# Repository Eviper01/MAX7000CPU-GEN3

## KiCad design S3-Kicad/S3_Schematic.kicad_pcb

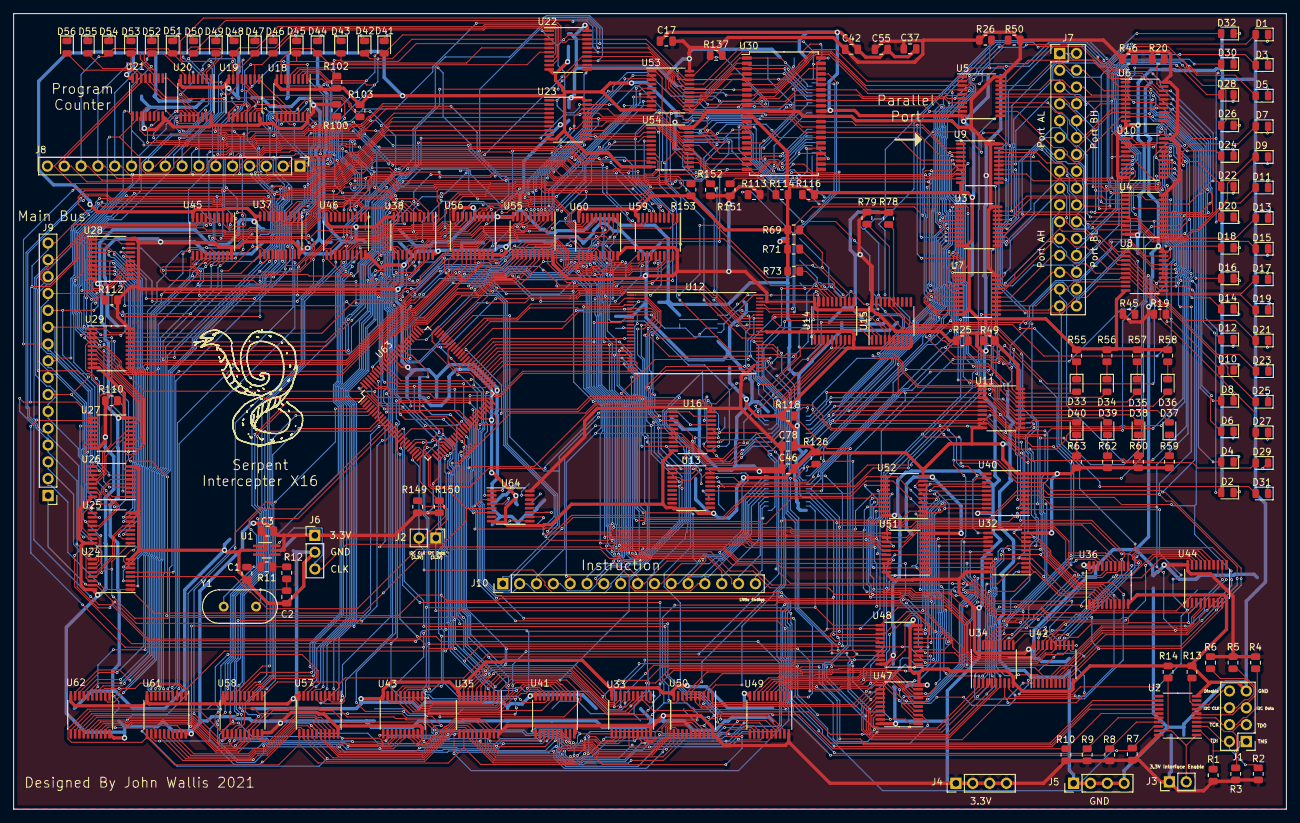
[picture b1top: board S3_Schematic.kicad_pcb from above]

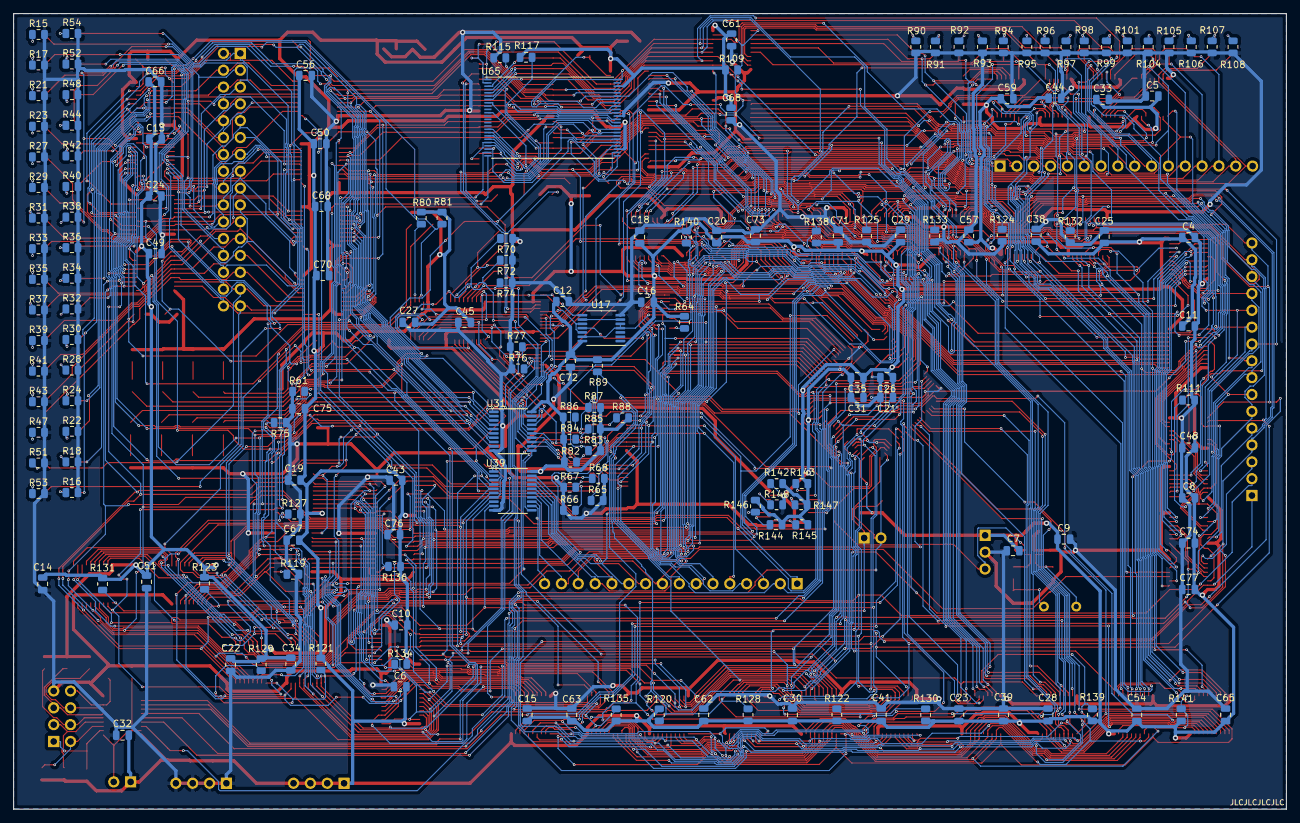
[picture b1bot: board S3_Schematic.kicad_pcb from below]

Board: 2 copper layers, 192.0 x 120.0 mm, 355 parts (167 on the bottom side), 363 nets.

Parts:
C1, C2: 32p; C_0805_2012Metric
C3, C4, C5, C6, C7, C8, C9, C10, C11, C12, C13, C14, C15, C16, C17, C18, C19, C20, C21, C22, C23, C24, C25, C26, C27, C28, C29, C30, C31, C32, C33, C34, C35, C37, C38, C39, C41, C42, C43, C44, C45, C46, C48, C49, C50, C51, C54, C55, C56, C57, C59, C60, C61, C62, C63, C65, C66, C67, C68, C71, C72, C73, C74, C75, C76, C77, C78: 100n; C_0805_2012Metric
C70: 100; C_0805_2012Metric
D1, D2, D3, D4, D5, D6, D7, D8, D9, D10, D11, D12, D13, D14, D15, D16, D17, D18, D19, D20, D21, D22, D23, D24, D25, D26, D27, D28, D29, D30, D31, D32, D33, D34, D35, D36, D37, D38, D39, D40, D41, D42, D43, D44, D45, D46, D47, D48, D49, D50, D51, D52, D53, D54, D55, D56: LED; LED_0805_2012Metric
J1: Conn_02x04_Counter_Clockwise; PinHeader_2x04_P2.54mm_Vertical
J2, J3: Conn_01x02; PinHeader_1x02_P2.54mm_Vertical
J4, J5: Conn_01x04; PinHeader_1x04_P2.54mm_Vertical
J6: Conn_01x03; PinHeader_1x03_P2.54mm_Vertical
J7: Conn_02x16_Odd_Even; PinHeader_2x16_P2.54mm_Vertical
J8, J9, J10: Conn_01x16; PinHeader_1x16_P2.54mm_Vertical
R1, R2, R3, R4, R5, R6, R7, R8, R9, R10, R13, R14, R19, R20, R25, R26, R45, R46, R49, R50, R61, R64, R65, R66, R67, R68, R69, R70, R71, R72, R73, R74, R75, R76, R77, R78, R79, R80, R81, R82, R83, R84, R85, R86, R87, R88, R89, R100, R102, R103, R109, R110, R111, R112, R113, R114, R115, R116, R117, R118, R119, R120, R121, R122, R123, R124, R125, R126, R127, R128, R129, R130, R131, R132, R133, R134, R135, R136, R137, R138, R139, R140, R141, R142, R143, R144, R145, R146, R147, R148, R149, R150, R151, R152, R153: 50K; R_0805_2012Metric
R11: 2.2M; R_0805_2012Metric
R12: 1k; R_0805_2012Metric
R15, R16, R17, R18, R21, R22, R23, R24, R27, R28, R29, R30, R31, R32, R33, R34, R35, R36, R37, R38, R39, R40, R41, R42, R43, R44, R47, R48, R51, R52, R53, R54, R55, R56, R57, R58, R59, R60, R62, R63, R90, R91, R92, R93, R94, R95, R96, R97, R98, R99, R101, R104, R105, R106, R107, R108: 330; R_0805_2012Metric
U1: SN74LVC1GX04DCKR; SOT-363_SC-70-6_Handsoldering
U2, U4, U6, U8, U10, U13, U14, U15, U16, U22, U23, U28, U29, U47, U48, U49, U50, U51, U52, U53, U54, U55, U56, U57, U58, U59, U60, U61, U62: 74HC541; TSSOP-20_4.4x6.5mm_P0.65mm
U3, U5, U7, U9, U11, U31, U32, U33, U34, U35, U36, U37, U38, U39, U40, U41, U42, U43, U44, U45, U46: 74HC574; TSSOP-20_4.4x6.5mm_P0.65mm
U12, U65: SST39VF800A-70-4C-EKE; TSOP-I-48_18.4x12mm_P0.5mm
U17: 74HC00; TSSOP-14_4.4x5mm_P0.65mm
U18, U19, U20, U21, U24, U25, U26, U27, U64: 74hc193; TSSOP-16_4.4x5mm_P0.65mm
U30: CY62136EV30LL-45ZSXI; TSOP-II-44_10.16x18.41mm_P0.8mm
U63: XC9572XL-10TQG100C; TQFP-100_14x14mm_P0.5mm
Y1: Crystal; Crystal_HC49-U_Vertical

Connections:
+3V3: C3.1, C4.1, C5.1, C6.1, C7.1, C8.1, C9.1, C10.1, C11.1, C12.1, C13.1, C14.1, C15.1, C16.1, C17.1, C18.1, C19.1, C20.1, C21.1, C22.1, C23.1, C24.1, C25.1, C26.1, C27.1, C28.1, C29.1, C30.1, C31.1, C32.1, C33.1, C34.1, C35.1, C37.1, C38.1, C39.1, C41.1, C42.1, C43.1, C44.1, C45.1, C46.1, C48.1, C49.1, C50.1, C51.1, C54.1, C55.1, C56.1, C57.1, C59.1, C60.1, C61.1, C62.1, C63.1, C65.1, C66.1, C67.1, C68.1, C70.1, C71.1, C72.1, C73.1, C74.1, C75.1, C76.1, C77.1, C78.1, J3.1, J4.1, J4.2, J4.3, J4.4, J6.1, R1.1, R2.1, R3.1, R4.1, R5.1, R6.1, R7.1, R8.1, R9.1, R10.1, R19.1, R20.1, R25.1, R26.1, R45.1, R46.1, R49.1, R50.1, R64.1, R78.1, R79.1, R80.1, R81.1, R82.1, R83.1, R84.1, R85.1, R86.1, R87.1, R88.1, R89.1, R100.1, R109.2, R110.1, R112.2, R113.2, R117.2, R120.2, R121.2, R122.2, R123.2, R128.2, R129.2, R130.2, R131.2, R134.1, R135.1, R136.1, R137.1, R138.1, R139.1, R140.1, R141.1, R142.1, R143.1, R144.1, R145.1, R146.1, R147.1, R149.1, R150.1, R151.1, R152.1, U1.5, U2.20, U3.20, U4.20, U5.20, U6.20, U7.20, U8.20, U9.20, U10.20, U11.20, U12.27, U12.46, U13.20, U14.20, U15.20, U16.20, U17.14, U18.16, U19.16, U20.16, U21.16, U22.20, U23.20, U24.16, U25.16, U26.16, U27.16, U28.20, U29.20, U30.11, U30.33, U31.20, U32.20, U33.20, U34.20, U35.20, U36.20, U37.20, U38.20, U39.20, U40.20, U41.20, U42.20, U43.20, U44.20, U45.20, U46.20, U47.20, U48.20, U49.20, U50.20, U51.20, U52.20, U53.20, U54.20, U55.20, U56.20, U57.20, U58.20, U59.20, U60.20, U61.20, U62.20, U63.26, U63.38, U63.51, U63.88, U64.16, U65.27, U65.46
/ALU/B0: J9.1, U3.2, U4.18, U5.2, U6.18, U11.2, U24.15, U30.7, U31.2, U32.2, U33.2, U34.2, U35.2, U36.2, U37.2, U38.2, U47.18, U63.52, U65.45
/ALU/B1: J9.2, U3.3, U4.17, U5.3, U6.17, U11.3, U24.1, U30.8, U31.3, U32.3, U33.3, U34.3, U35.3, U36.3, U37.3, U38.3, U47.17, U63.50, U65.44
/ALU/B2: J9.3, U3.4, U4.16, U5.4, U6.16, U11.4, U24.10, U30.9, U31.4, U32.4, U33.4, U34.4, U35.4, U36.4, U37.4, U38.4, U47.16, U63.49, U65.43
/ALU/B3: J9.4, U3.5, U4.15, U5.5, U6.15, U11.5, U24.9, U30.10, U31.5, U32.5, U33.5, U34.5, U35.5, U36.5, U37.5, U38.5, U47.15, U63.42, U65.42
/ALU/B4: J9.5, U3.6, U4.14, U5.6, U6.14, U11.6, U25.15, U30.38, U31.6, U32.6, U33.6, U34.6, U35.6, U36.6, U37.6, U38.6, U47.14, U63.41, U65.41
/ALU/B5: J9.6, U3.7, U4.13, U5.7, U6.13, U11.7, U25.1, U30.37, U31.7, U32.7, U33.7, U34.7, U35.7, U36.7, U37.7, U38.7, U47.13, U63.40, U65.40
/ALU/B6: J9.7, U3.8, U4.12, U5.8, U6.12, U11.8, U25.10, U30.36, U31.8, U32.8, U33.8, U34.8, U35.8, U36.8, U37.8, U38.8, U47.12, U63.39, U65.39
/ALU/B7: J9.8, U3.9, U4.11, U5.9, U6.11, U11.9, U25.9, U30.35, U31.9, U32.9, U33.9, U34.9, U35.9, U36.9, U37.9, U38.9, U47.11, U63.37, U65.38
/ALU/B8: J9.9, U7.2, U8.18, U9.2, U10.18, U26.15, U30.32, U39.2, U40.2, U41.2, U42.2, U43.2, U44.2, U45.2, U46.2, U48.18, U63.36, U65.36
/ALU/B9: J9.10, U7.3, U8.17, U9.3, U10.17, U26.1, U30.31, U39.3, U40.3, U41.3, U42.3, U43.3, U44.3, U45.3, U46.3, U48.17, U63.35, U65.35
/ALU/B10: J9.11, U7.4, U8.16, U9.4, U10.16, U26.10, U30.30, U39.4, U40.4, U41.4, U42.4, U43.4, U44.4, U45.4, U46.4, U48.16, U63.33, U65.34
/ALU/B11: J9.12, U7.5, U8.15, U9.5, U10.15, U26.9, U30.29, U39.5, U40.5, U41.5, U42.5, U43.5, U44.5, U45.5, U46.5, U48.15, U63.32, U65.33
/ALU/B12: J9.13, U7.6, U8.14, U9.6, U10.14, U27.15, U30.16, U39.6, U40.6, U41.6, U42.6, U43.6, U44.6, U45.6, U46.6, U48.14, U63.30, U65.32
/ALU/B13: J9.14, U7.7, U8.13, U9.7, U10.13, U27.1, U30.15, U39.7, U40.7, U41.7, U42.7, U43.7, U44.7, U45.7, U46.7, U48.13, U63.29, U65.31
/ALU/B14: J9.15, U7.8, U8.12, U9.8, U10.12, U27.10, U30.14, U39.8, U40.8, U41.8, U42.8, U43.8, U44.8, U45.8, U46.8, U48.12, U63.28, U65.30
/ALU/B15: J9.16, U7.9, U8.11, U9.9, U10.11, U27.9, U30.13, U39.9, U40.9, U41.9, U42.9, U43.9, U44.9, U45.9, U46.9, U48.11, U63.27, U65.29
/ALU/EvenR0: U34.19, U36.19, U51.18, U55.18, U59.18, U63.71
/ALU/EvenR1: U34.18, U36.18, U51.17, U55.17, U59.17, U63.72
/ALU/EvenR2: U34.17, U36.17, U51.16, U55.16, U59.16, U63.74
/ALU/EvenR3: U34.16, U36.16, U51.15, U55.15, U59.15, U63.76
/ALU/EvenR4: U34.15, U36.15, U51.14, U55.14, U59.14, U63.77
/ALU/EvenR5: U34.14, U36.14, U51.13, U55.13, U59.13, U63.78
/ALU/EvenR6: U34.13, U36.13, U51.12, U55.12, U59.12, U63.79
/ALU/EvenR7: U34.12, U36.12, U51.11, U55.11, U59.11, U63.81
/ALU/EvenR8: U42.19, U44.19, U52.18, U56.18, U60.18, U63.82
/ALU/EvenR9: U42.18, U44.18, U52.17, U56.17, U60.17, U63.85
/ALU/EvenR10: U42.17, U44.17, U52.16, U56.16, U60.16, U63.86
/ALU/EvenR11: U42.16, U44.16, U52.15, U56.15, U60.15, U63.87
/ALU/EvenR12: U42.15, U44.15, U52.14, U56.14, U60.14, U63.89
/ALU/EvenR13: U42.14, U44.14, U52.13, U56.13, U60.13, U63.90
/ALU/EvenR14: U42.13, U44.13, U52.12, U56.12, U60.12, U63.91
/ALU/EvenR15: U42.12, U44.12, U52.11, U56.11, U60.11, U63.92
/ALU/Ins0: J10.1, U12.48, U13.2, U14.2, U15.2, U16.2, U31.19, U63.70
/ALU/Ins1: J10.2, U12.1, U13.3, U14.3, U15.3, U16.3, U31.18, U63.68
/ALU/Ins2: J10.3, U12.2, U13.4, U14.4, U15.4, U16.4, U31.17, U63.67
/ALU/Ins3: J10.4, U12.3, U13.5, U14.5, U15.5, U16.5, U31.16, U63.66
/ALU/Ins4: J10.5, U12.4, U14.6, U16.6, U31.15, U63.65
/ALU/Ins5: J10.6, U12.5, U14.7, U16.7, U31.14, U63.64
/ALU/Ins6: J10.7, U12.6, U14.8, U16.8, U31.13, U63.63
/ALU/Ins7: J10.8, U12.7, U16.9, U17.4, U17.5, U17.13, U31.12, U63.61
/ALU/Ins8: J10.9, U12.8, U39.19, U63.60
/ALU/Ins9: J10.10, U12.16, U39.18, U63.59
/ALU/Ins10: J10.11, U12.17, U39.17, U63.58
/ALU/Ins11: J10.12, U12.18, U39.16, U63.57
/ALU/Ins12: J10.13, U12.19, U39.15, U63.56
/ALU/Ins13: J10.14, U12.20, U39.14, U63.55
/ALU/Ins14: J10.15, U12.21, U39.13, U63.54
/ALU/Ins15: J10.16, U12.22, U39.12, U63.53
/ALU/OddR0: U33.19, U35.19, U49.18, U57.18, U61.18, U63.18
/ALU/OddR1: U33.18, U35.18, U49.17, U57.17, U61.17, U63.17
/ALU/OddR2: U33.17, U35.17, U49.16, U57.16, U61.16, U63.16
/ALU/OddR3: U33.16, U35.16, U49.15, U57.15, U61.15, U63.15
/ALU/OddR4: U33.15, U35.15, U49.14, U57.14, U61.14, U63.14
/ALU/OddR5: U33.14, U35.14, U49.13, U57.13, U61.13, U63.13
/ALU/OddR6: U33.13, U35.13, U49.12, U57.12, U61.12, U63.12
/ALU/OddR7: U33.12, U35.12, U49.11, U57.11, U61.11, U63.11
/ALU/OddR8: U41.19, U43.19, U50.18, U58.18, U62.18, U63.10
/ALU/OddR9: U41.18, U43.18, U50.17, U58.17, U62.17, U63.9
/ALU/OddR10: U41.17, U43.17, U50.16, U58.16, U62.16, U63.8
/ALU/OddR11: U41.16, U43.16, U50.15, U58.15, U62.15, U63.6
/ALU/OddR12: U41.15, U43.15, U50.14, U58.14, U62.14, U63.5
/ALU/OddR13: U41.14, U43.14, U50.13, U58.13, U62.13, U63.4
/ALU/OddR14: U41.13, U43.13, U50.12, U58.12, U62.12, U63.3
/ALU/OddR15: U41.12, U43.12, U50.11, U58.11, U62.11, U63.1
/ALU/State0: U12.23, U63.99, U64.3
/ALU/State1: U12.24, U63.98, U64.2
/ALU/State2: U12.25, U63.97, U64.6
/Boot Flash/MA0: U22.18, U28.18, U30.42, U53.18, U65.48
/Boot Flash/MA1: U22.17, U28.17, U30.43, U53.17, U65.1
/Boot Flash/MA2: U22.16, U28.16, U30.44, U53.16, U65.2
/Boot Flash/MA3: U22.15, U28.15, U30.1, U53.15, U65.3
/Boot Flash/MA4: U22.14, U28.14, U30.2, U53.14, U65.4
/Boot Flash/MA5: U22.13, U28.13, U30.3, U53.13, U65.5
/Boot Flash/MA6: U22.12, U28.12, U30.4, U53.12, U65.6
/Boot Flash/MA7: U22.11, U28.11, U30.5, U53.11, U65.7
/Boot Flash/MA8: U23.18, U29.18, U30.18, U54.18, U65.8
/Boot Flash/MA9: U23.17, U29.17, U30.19, U54.17, U65.16
/Boot Flash/MA10: U23.16, U29.16, U30.20, U54.16, U65.17
/Boot Flash/MA11: U23.15, U29.15, U30.21, U54.15, U65.18
/Boot Flash/MA12: U23.14, U29.14, U30.22, U54.14, U65.19
/Boot Flash/MA13: U23.13, U29.13, U30.25, U54.13, U65.20
/Boot Flash/MA14: U23.12, U29.12, U30.26, U54.12, U65.21
/Boot Flash/MA15: U23.11, U29.11, U30.27, U54.11, U65.22
/GPIO/P0: D1.2, J7.1, U3.19, U4.2
/GPIO/P1: D3.2, J7.3, U3.18, U4.3
/GPIO/P2: D5.2, J7.5, U3.17, U4.4
/GPIO/P3: D7.2, J7.7, U3.16, U4.5
/GPIO/P4: D9.2, J7.9, U3.15, U4.6
/GPIO/P5: D11.2, J7.11, U3.14, U4.7
/GPIO/P6: D13.2, J7.13, U3.13, U4.8
/GPIO/P7: D15.2, J7.15, U3.12, U4.9
/GPIO/P8: D17.2, J7.17, U7.19, U8.2
/GPIO/P9: D19.2, J7.19, U7.18, U8.3
/GPIO/P10: D21.2, J7.21, U7.17, U8.4
/GPIO/P11: D23.2, J7.23, U7.16, U8.5
/GPIO/P12: D25.2, J7.25, U7.15, U8.6
/GPIO/P13: D27.2, J7.27, U7.14, U8.7
/GPIO/P14: D29.2, J7.29, U7.13, U8.8
/GPIO/P15: D31.2, J7.31, U7.12, U8.9
/GPIO/P16: D32.2, J7.32, U9.12, U10.9
/GPIO/P17: D30.2, J7.30, U9.13, U10.8
/GPIO/P18: D28.2, J7.28, U9.14, U10.7
/GPIO/P19: D26.2, J7.26, U9.15, U10.6
/GPIO/P20: D24.2, J7.24, U9.16, U10.5
/GPIO/P21: D22.2, J7.22, U9.17, U10.4
/GPIO/P22: D20.2, J7.20, U9.18, U10.3
/GPIO/P23: D18.2, J7.18, U9.19, U10.2
/GPIO/P24: D16.2, J7.16, U5.12, U6.9
/GPIO/P25: D14.2, J7.14, U5.13, U6.8
/GPIO/P26: D12.2, J7.12, U5.14, U6.7
/GPIO/P27: D10.2, J7.10, U5.15, U6.6
/GPIO/P28: D8.2, J7.8, U5.16, U6.5
/GPIO/P29: D6.2, J7.6, U5.17, U6.4
/GPIO/P30: D4.2, J7.4, U5.18, U6.3
/GPIO/P31: D2.2, J7.2, U5.19, U6.2
/ProgramCounter/JB0: U18.15, U37.19, U59.2, U61.2
/ProgramCounter/JB1: U18.1, U37.18, U59.3, U61.3
/ProgramCounter/JB2: U18.10, U37.17, U59.4, U61.4
/ProgramCounter/JB3: U18.9, U37.16, U59.5, U61.5
/ProgramCounter/JB4: U19.15, U37.15, U59.6, U61.6
/ProgramCounter/JB5: U19.1, U37.14, U59.7, U61.7
/ProgramCounter/JB6: U19.10, U37.13, U59.8, U61.8
/ProgramCounter/JB7: U19.9, U37.12, U59.9, U61.9
/ProgramCounter/JB8: U20.15, U45.19, U60.2, U62.2
/ProgramCounter/JB9: U20.1, U45.18, U60.3, U62.3
/ProgramCounter/JB10: U20.10, U45.17, U60.4, U62.4
/ProgramCounter/JB11: U20.9, U45.16, U60.5, U62.5
/ProgramCounter/JB12: U21.15, U45.15, U60.6, U62.6
/ProgramCounter/JB13: U21.1, U45.14, U60.7, U62.7
/ProgramCounter/JB14: U21.10, U45.13, U60.8, U62.8
/ProgramCounter/JB15: U21.9, U45.12, U60.9, U62.9
/ProgramCounter/PC0: D41.2, J8.1, U18.3, U22.2
/ProgramCounter/PC1: D42.2, J8.2, U18.2, U22.3
/ProgramCounter/PC2: D43.2, J8.3, U18.6, U22.4
/ProgramCounter/PC3: D44.2, J8.4, U18.7, U22.5
/ProgramCounter/PC4: D45.2, J8.5, U19.3, U22.6
/ProgramCounter/PC5: D46.2, J8.6, U19.2, U22.7
/ProgramCounter/PC6: D47.2, J8.7, U19.6, U22.8
/ProgramCounter/PC7: D48.2, J8.8, U19.7, U22.9
/ProgramCounter/PC8: D49.2, J8.9, U20.3, U23.2
/ProgramCounter/PC9: D50.2, J8.10, U20.2, U23.3
/ProgramCounter/PC10: D51.2, J8.11, U20.6, U23.4
/ProgramCounter/PC11: D52.2, J8.12, U20.7, U23.5
/ProgramCounter/PC12: D53.2, J8.13, U21.3, U23.6
/ProgramCounter/PC13: D54.2, J8.14, U21.2, U23.7
/ProgramCounter/PC14: D55.2, J8.15, U21.6, U23.8
/ProgramCounter/PC15: D56.2, J8.16, U21.7, U23.9
/Registers/Acc0: U32.19, U47.2, U49.2, U51.2
/Registers/Acc1: U32.18, U47.3, U49.3, U51.3
/Registers/Acc2: U32.17, U47.4, U49.4, U51.4
/Registers/Acc3: U32.16, U47.5, U49.5, U51.5
/Registers/Acc4: U32.15, U47.6, U49.6, U51.6
/Registers/Acc5: U32.14, U47.7, U49.7, U51.7
/Registers/Acc6: U32.13, U47.8, U49.8, U51.8
/Registers/Acc7: U32.12, U47.9, U49.9, U51.9
/Registers/Acc8: U40.19, U48.2, U50.2, U52.2
/Registers/Acc9: U40.18, U48.3, U50.3, U52.3
/Registers/Acc10: U40.17, U48.4, U50.4, U52.4
/Registers/Acc11: U40.16, U48.5, U50.5, U52.5
/Registers/Acc12: U40.15, U48.6, U50.6, U52.6
/Registers/Acc13: U40.14, U48.7, U50.7, U52.7
/Registers/Acc14: U40.13, U48.8, U50.8, U52.8
/Registers/Acc15: U40.12, U48.9, U50.9, U52.9
/Registers/RA0: U38.19, U53.2, U55.2, U57.2
/Registers/RA1: U38.18, U53.3, U55.3, U57.3
/Registers/RA2: U38.17, U53.4, U55.4, U57.4
/Registers/RA3: U38.16, U53.5, U55.5, U57.5
/Registers/RA4: U38.15, U53.6, U55.6, U57.6
/Registers/RA5: U38.14, U53.7, U55.7, U57.7
/Registers/RA6: U38.13, U53.8, U55.8, U57.8
/Registers/RA7: U38.12, U53.9, U55.9, U57.9
/Registers/RA8: U46.19, U54.2, U56.2, U58.2
/Registers/RA9: U46.18, U54.3, U56.3, U58.3
/Registers/RA10: U46.17, U54.4, U56.4, U58.4
/Registers/RA11: U46.16, U54.5, U56.5, U58.5
/Registers/RA12: U46.15, U54.6, U56.6, U58.6
/Registers/RA13: U46.14, U54.7, U56.7, U58.7
/Registers/RA14: U46.13, U54.8, U56.8, U58.8
/Registers/RA15: U46.12, U54.9, U56.9, U58.9
/StackPointer/SP0: U24.3, U28.2
/StackPointer/SP1: U24.2, U28.3
/StackPointer/SP2: U24.6, U28.4
/StackPointer/SP3: U24.7, U28.5
/StackPointer/SP4: U25.3, U28.6
/StackPointer/SP5: U25.2, U28.7
/StackPointer/SP6: U25.6, U28.8
/StackPointer/SP7: U25.7, U28.9
/StackPointer/SP8: U26.3, U29.2
/StackPointer/SP9: U26.2, U29.3
/StackPointer/SP10: U26.6, U29.4
/StackPointer/SP11: U26.7, U29.5
/StackPointer/SP12: U27.3, U29.6
/StackPointer/SP13: U27.2, U29.7
/StackPointer/SP14: U27.6, U29.8
/StackPointer/SP15: U27.7, U29.9
CLK: J6.3, U1.6, U63.22, U64.5
CounterClear: R103.2, U18.14, U19.14, U20.14, U21.14
CounterUp: U12.42, U18.5
DDR_Load: R75.2, U11.11, U14.18
FLASHPAGE0: D39.2, U11.13, U65.23
FLASHPAGE1: D38.2, U11.14, U65.24
FLASHPAGE2: D37.2, U11.15, U65.25
FlashOut: R152.2, U12.36, U65.28
GND: C1.2, C2.2, C3.2, C4.2, C5.2, C6.2, C7.2, C8.2, C9.2, C10.2, C11.2, C12.2, C13.2, C14.2, C15.2, C16.2, C17.2, C18.2, C19.2, C20.2, C21.2, C22.2, C23.2, C24.2, C25.2, C26.2, C27.2, C28.2, C29.2, C30.2, C31.2, C32.2, C33.2, C34.2, C35.2, C37.2, C38.2, C39.2, C41.2, C42.2, C43.2, C44.2, C45.2, C46.2, C48.2, C49.2, C50.2, C51.2, C54.2, C55.2, C56.2, C57.2, C59.2, C60.2, C61.2, C62.2, C63.2, C65.2, C66.2, C67.2, C68.2, C70.2, C71.2, C72.2, C73.2, C74.2, C75.2, C76.2, C77.2, C78.2, J1.7, J5.1, J5.2, J5.3, J5.4, J6.2, R13.2, R14.2, R15.2, R16.2, R17.2, R18.2, R21.2, R22.2, R23.2, R24.2, R27.2, R28.2, R29.2, R30.2, R31.2, R32.2, R33.2, R34.2, R35.2, R36.2, R37.2, R38.2, R39.2, R40.2, R41.2, R42.2, R43.2, R44.2, R47.2, R48.2, R51.2, R52.2, R53.2, R54.2, R55.2, R56.2, R57.2, R58.2, R59.2, R60.2, R61.1, R62.2, R63.2, R65.1, R66.1, R67.1, R68.1, R69.1, R70.1, R71.1, R72.1, R73.1, R74.1, R75.1, R76.1, R77.1, R90.2, R91.2, R92.2, R93.2, R94.2, R95.2, R96.2, R97.2, R98.2, R99.2, R101.2, R102.1, R103.1, R104.2, R105.2, R106.2, R107.2, R108.2, R111.1, R114.2, R115.2, R116.2, R118.2, R119.2, R124.2, R125.2, R126.2, R127.2, R132.2, R133.2, R148.1, R153.1, U1.2, U2.10, U3.10, U4.10, U5.10, U6.10, U7.10, U8.10, U9.10, U10.10, U11.10, U12.37, U13.10, U14.10, U15.10, U16.10, U17.7, U18.8, U19.8, U20.8, U21.8, U22.10, U23.10, U24.8, U25.8, U26.8, U27.8, U28.10, U29.10, U30.12, U30.34, U31.10, U32.10, U33.10, U34.10, U35.10, U36.10, U37.10, U38.10, U39.10, U40.10, U41.10, U42.10, U43.10, U44.10, U45.10, U46.10, U47.10, U48.10, U49.10, U50.10, U51.10, U52.10, U53.10, U54.10, U55.10, U56.10, U57.10, U58.10, U59.10, U60.10, U61.10, U62.10, U63.21, U63.31, U63.44, U63.62, U63.69, U63.75, U63.84, U63.100, U64.8, U65.37
InsRegControl: U12.34, U31.11, U39.11
MainRegReadControl: U12.33, U32.11, U40.11
unnamed: C1.1, R11.2, U1.3, Y1.1
unnamed: C2.1, R12.2, Y1.2
unnamed: D1.1, R15.1
unnamed: D2.1, R16.1
unnamed: D3.1, R17.1
unnamed: D4.1, R18.1
unnamed: D5.1, R21.1
unnamed: D6.1, R22.1
unnamed: D7.1, R23.1
unnamed: D8.1, R24.1
unnamed: D9.1, R27.1
unnamed: D10.1, R28.1
unnamed: D11.1, R29.1
unnamed: D12.1, R30.1
unnamed: D13.1, R31.1
unnamed: D14.1, R32.1
unnamed: D15.1, R33.1
unnamed: D16.1, R34.1
unnamed: D17.1, R35.1
unnamed: D18.1, R36.1
unnamed: D19.1, R37.1
unnamed: D20.1, R38.1
unnamed: D21.1, R39.1
unnamed: D22.1, R40.1
unnamed: D23.1, R41.1
unnamed: D24.1, R42.1
unnamed: D25.1, R43.1
unnamed: D26.1, R44.1
unnamed: D27.1, R47.1
unnamed: D28.1, R48.1
unnamed: D29.1, R51.1
unnamed: D30.1, R52.1
unnamed: D31.1, R53.1
unnamed: D32.1, R54.1
unnamed: D33.1, R55.1
unnamed: D34.1, R56.1
unnamed: D35.1, R57.1
unnamed: D36.1, R58.1
unnamed: D37.1, R59.1
unnamed: D38.1, R60.1
unnamed: D39.1, R62.1
unnamed: D40.1, R63.1
unnamed: D41.1, R90.1
unnamed: D42.1, R91.1
unnamed: D43.1, R92.1
unnamed: D44.1, R93.1
unnamed: D45.1, R94.1
unnamed: D46.1, R95.1
unnamed: D47.1, R96.1
unnamed: D48.1, R97.1
unnamed: D49.1, R98.1
unnamed: D50.1, R99.1
unnamed: D51.1, R101.1
unnamed: D52.1, R104.1
unnamed: D53.1, R105.1
unnamed: D54.1, R106.1
unnamed: D55.1, R107.1
unnamed: D56.1, R108.1
unnamed: J3.2, R14.1, U2.1, U2.19
unnamed: R11.1, R12.1, U1.4
unnamed: R61.2, U11.1
unnamed: R64.2, U12.11
unnamed: R76.2, U12.28
unnamed: R77.2, U12.26
unnamed: R102.2, U18.4
unnamed: R114.1, U30.40
unnamed: R115.1, U30.6
unnamed: R116.1, U30.39
unnamed: R119.1, U32.1
unnamed: R124.1, U37.1
unnamed: R125.1, U38.1
unnamed: R126.1, U39.1
unnamed: R127.1, U40.1
unnamed: R132.1, U45.1
unnamed: R133.1, U46.1
unnamed: R142.2, U64.15
unnamed: R143.2, U64.1
unnamed: R144.2, U64.10
unnamed: R145.2, U64.9
unnamed: R146.2, U64.11
unnamed: R147.2, U64.4
unnamed: R148.2, U64.14
unnamed: R151.2, U65.11
unnamed: R153.2, U65.26
unnamed: U17.6, U17.9
unnamed: U18.12, U19.5
unnamed: U18.13, U19.4
unnamed: U19.12, U20.5
unnamed: U19.13, U20.4
unnamed: U20.12, U21.5
unnamed: U20.13, U21.4
unnamed: U24.12, U25.5
unnamed: U24.13, U25.4
unnamed: U25.12, U26.5
unnamed: U25.13, U26.4
unnamed: U26.12, U27.5
unnamed: U26.13, U27.4
PS\2_CLK_3.3V: J2.2, R149.2, U2.13, U63.23
PS\2_CLK_5V: J1.6, R6.2, U2.7
PS\2_Data_3.3V: J2.1, R150.2, U2.14, U63.25
PS\2_Data_5V: J1.5, R5.2, U2.6
PortAWriteHigh: R67.2, U7.11, U13.17
PortAWriteLow: R68.2, U3.11, U13.18
PortBWriteHigh: R65.2, U9.11, U13.15
PortBWriteLow: R66.2, U5.11, U13.16
ProgramInsDisable: R118.1, U2.12, U31.1
ProgramInstructDisable_5V: J1.8, R13.1, U2.8
R1Control: R74.2, U14.17, U33.11, U41.11
R2Control: R73.2, U14.16, U34.11, U42.11
R3Control: R72.2, U14.15, U35.11, U43.11
R4Control: R71.2, U14.14, U36.11, U44.11
RAM_PAGE: D40.2, U11.12, U30.24
RJBControl: R70.2, U14.13, U37.11, U45.11
RMAControl: R69.2, U14.12, U38.11, U46.11
RegLatch: U12.43, U17.10, U17.12
StackClear: R111.2, U24.14, U25.14, U26.14, U27.14
StackDown: U12.41, U24.4
StackUp: U12.40, U24.5
TCK: R10.2, U2.15, U63.48
TCK_5V: J1.4, R4.2, U2.5
TDI: R8.2, U2.17, U63.45
TDI_5V: J1.2, R2.2, U2.3
TDO: R9.2, U2.16, U63.83
TDO_5V: J1.3, R3.2, U2.4
TMS: R7.2, U2.18, U63.47
TMS_5V: J1.1, R1.2, U2.2
~AHDD: D34.2, R49.2, U7.1, U11.18
~ALDD: D33.2, R25.2, U3.1, U11.19
~ALU_Enable: U16.1, U16.19, U63.20
~BHDD: D36.2, R50.2, U9.1, U11.16
~BLDD: D35.2, R26.2, U5.1, U11.17
~CounterLoad: R100.2, U18.11, U19.11, U20.11, U21.11, U63.95
~CounterOutEnable: R109.1, U12.35, U22.1, U22.19, U23.1, U23.19
~GeneralRegisterLatch: U14.1, U14.19, U17.8
~I-O_RegisterLatch: U13.1, U13.19, U17.11
~MainRegLeftOutput: R135.2, U12.29, U49.1, U49.19, U50.1, U50.19
~MainRegOutputControl: R134.2, U12.32, U47.1, U47.19, U48.1, U48.19
~MainRegRightOutput: R136.2, U51.1, U51.19, U52.1, U52.19, U63.96
~MemOutEnable: R113.1, U12.45, U30.41
~MemWriteControl: R117.1, U12.44, U30.17
~PortAReadHigh: R45.2, R79.2, U8.1, U8.19, U15.16
~PortAReadLow: R19.2, R78.2, U4.1, U4.19, U15.15
~PortBReadHigh: R46.2, R81.2, U10.1, U10.19, U15.18
~PortBReadLow: R20.2, R80.2, U6.1, U6.19, U15.17
~PortEnable: U12.30, U15.1, U15.19
~R1Out: R89.2, R120.1, R128.1, U16.18, U33.1, U41.1
~R2Out: R85.2, R121.1, R129.1, U16.14, U34.1, U42.1
~R3Out: R88.2, R122.1, R130.1, U16.17, U35.1, U43.1
~R4Out: R84.2, R123.1, R131.1, U16.13, U36.1, U44.1
~RJBLeftOutput: R87.2, R141.2, U16.16, U61.1, U61.19, U62.1, U62.19
~RJBRightOutput: R83.2, R140.2, U16.12, U59.1, U59.19, U60.1, U60.19
~RMALeftOutput: R86.2, R139.2, U16.15, U57.1, U57.19, U58.1, U58.19
~RMARightOutput: R82.2, R138.2, U16.11, U55.1, U55.19, U56.1, U56.19
~RamAddrEnable: R137.2, U12.31, U53.1, U53.19, U54.1, U54.19
~StackLoad: R110.2, U12.39, U24.11, U25.11, U26.11, U27.11
~StackOut: R112.1, U12.38, U28.1, U28.19, U29.1, U29.19

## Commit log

2021-10-10 "Initalisizing"
2021-10-11 registers bank
2021-10-15 3.3V parts
2021-10-22 Most of CPU planned out
2021-10-24 some weekend changes
2021-10-25 Schematic Done
2021-11-12 Circuit Board Drafted (it could probably be improved)
2021-11-17 began adding the HDL files
